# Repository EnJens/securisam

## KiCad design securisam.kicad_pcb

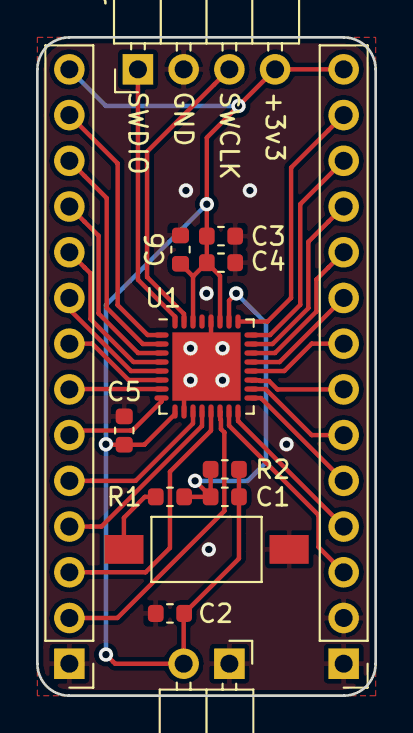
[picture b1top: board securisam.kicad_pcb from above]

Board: 2 copper layers, 18.8 x 36.6 mm, 14 parts (0 on the bottom side), 29 nets.

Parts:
C1: 100pF; C_0603_1608Metric
C2: 10uF; C_0603_1608Metric
C3: 1uF; C_0603_1608Metric
C4, C5, C6: 100nF; C_0603_1608Metric
J1: Conn_01x04; PinHeader_1x04_P2.54mm_Horizontal
J2, J3: Conn_01x14; PinHeader_1x14_P2.54mm_Vertical
J4: Conn_01x02; PinHeader_1x02_P2.54mm_Horizontal
R1: 330R; R_0603_1608Metric
R2: 2.2k; R_0603_1608Metric
SW1: RESET; SW_SPST_FSMSM
U1: ATSAML11E15A-MU; QFN-32-1EP_5x5mm_P0.5mm_EP3.8x3.8mm

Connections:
/PA00: J2.13, U1.1
/PA01: J2.12, U1.2
/PA02: J2.11, U1.3
/PA03: J2.10, U1.4
/PA04: J2.9, U1.5
/PA05: J2.8, U1.6
/PA06: J2.7, U1.7
/PA07: J2.6, U1.8
/PA08: J2.5, U1.11
/PA09: J2.4, U1.12
/PA10: J2.3, U1.13
/PA11: J2.2, U1.14
/PA14: J3.3, U1.15
/PA15: J3.4, U1.16
/PA16: J3.5, U1.17
/PA17: J3.6, U1.18
/PA18: J3.7, U1.19
/PA19: J3.8, U1.20
/PA22: J3.9, U1.21
/PA23: J3.10, U1.22
/PA24: J3.11, U1.23
/PA25: J3.12, U1.24
/PA27: J3.13, U1.25
/SWCLK: J1.3, U1.31
/SWDIO: J1.1, U1.32
/~RESET~: C1.2, R1.1, R2.2, U1.26
GND: C2.2, C3.2, C4.2, C5.2, C6.2, J1.2, J2.1, J3.1, J3.2, J4.1, SW1.1, U1.10, U1.28, U1.33
unnamed: R1.2, SW1.2
VDD: C1.1, C2.1, C3.1, C4.1, C5.1, C6.1, J1.4, J2.14, J3.14, J4.2, R2.1, U1.9, U1.27, U1.30

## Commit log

2018-07-16 ATSAM L11 breakout board
